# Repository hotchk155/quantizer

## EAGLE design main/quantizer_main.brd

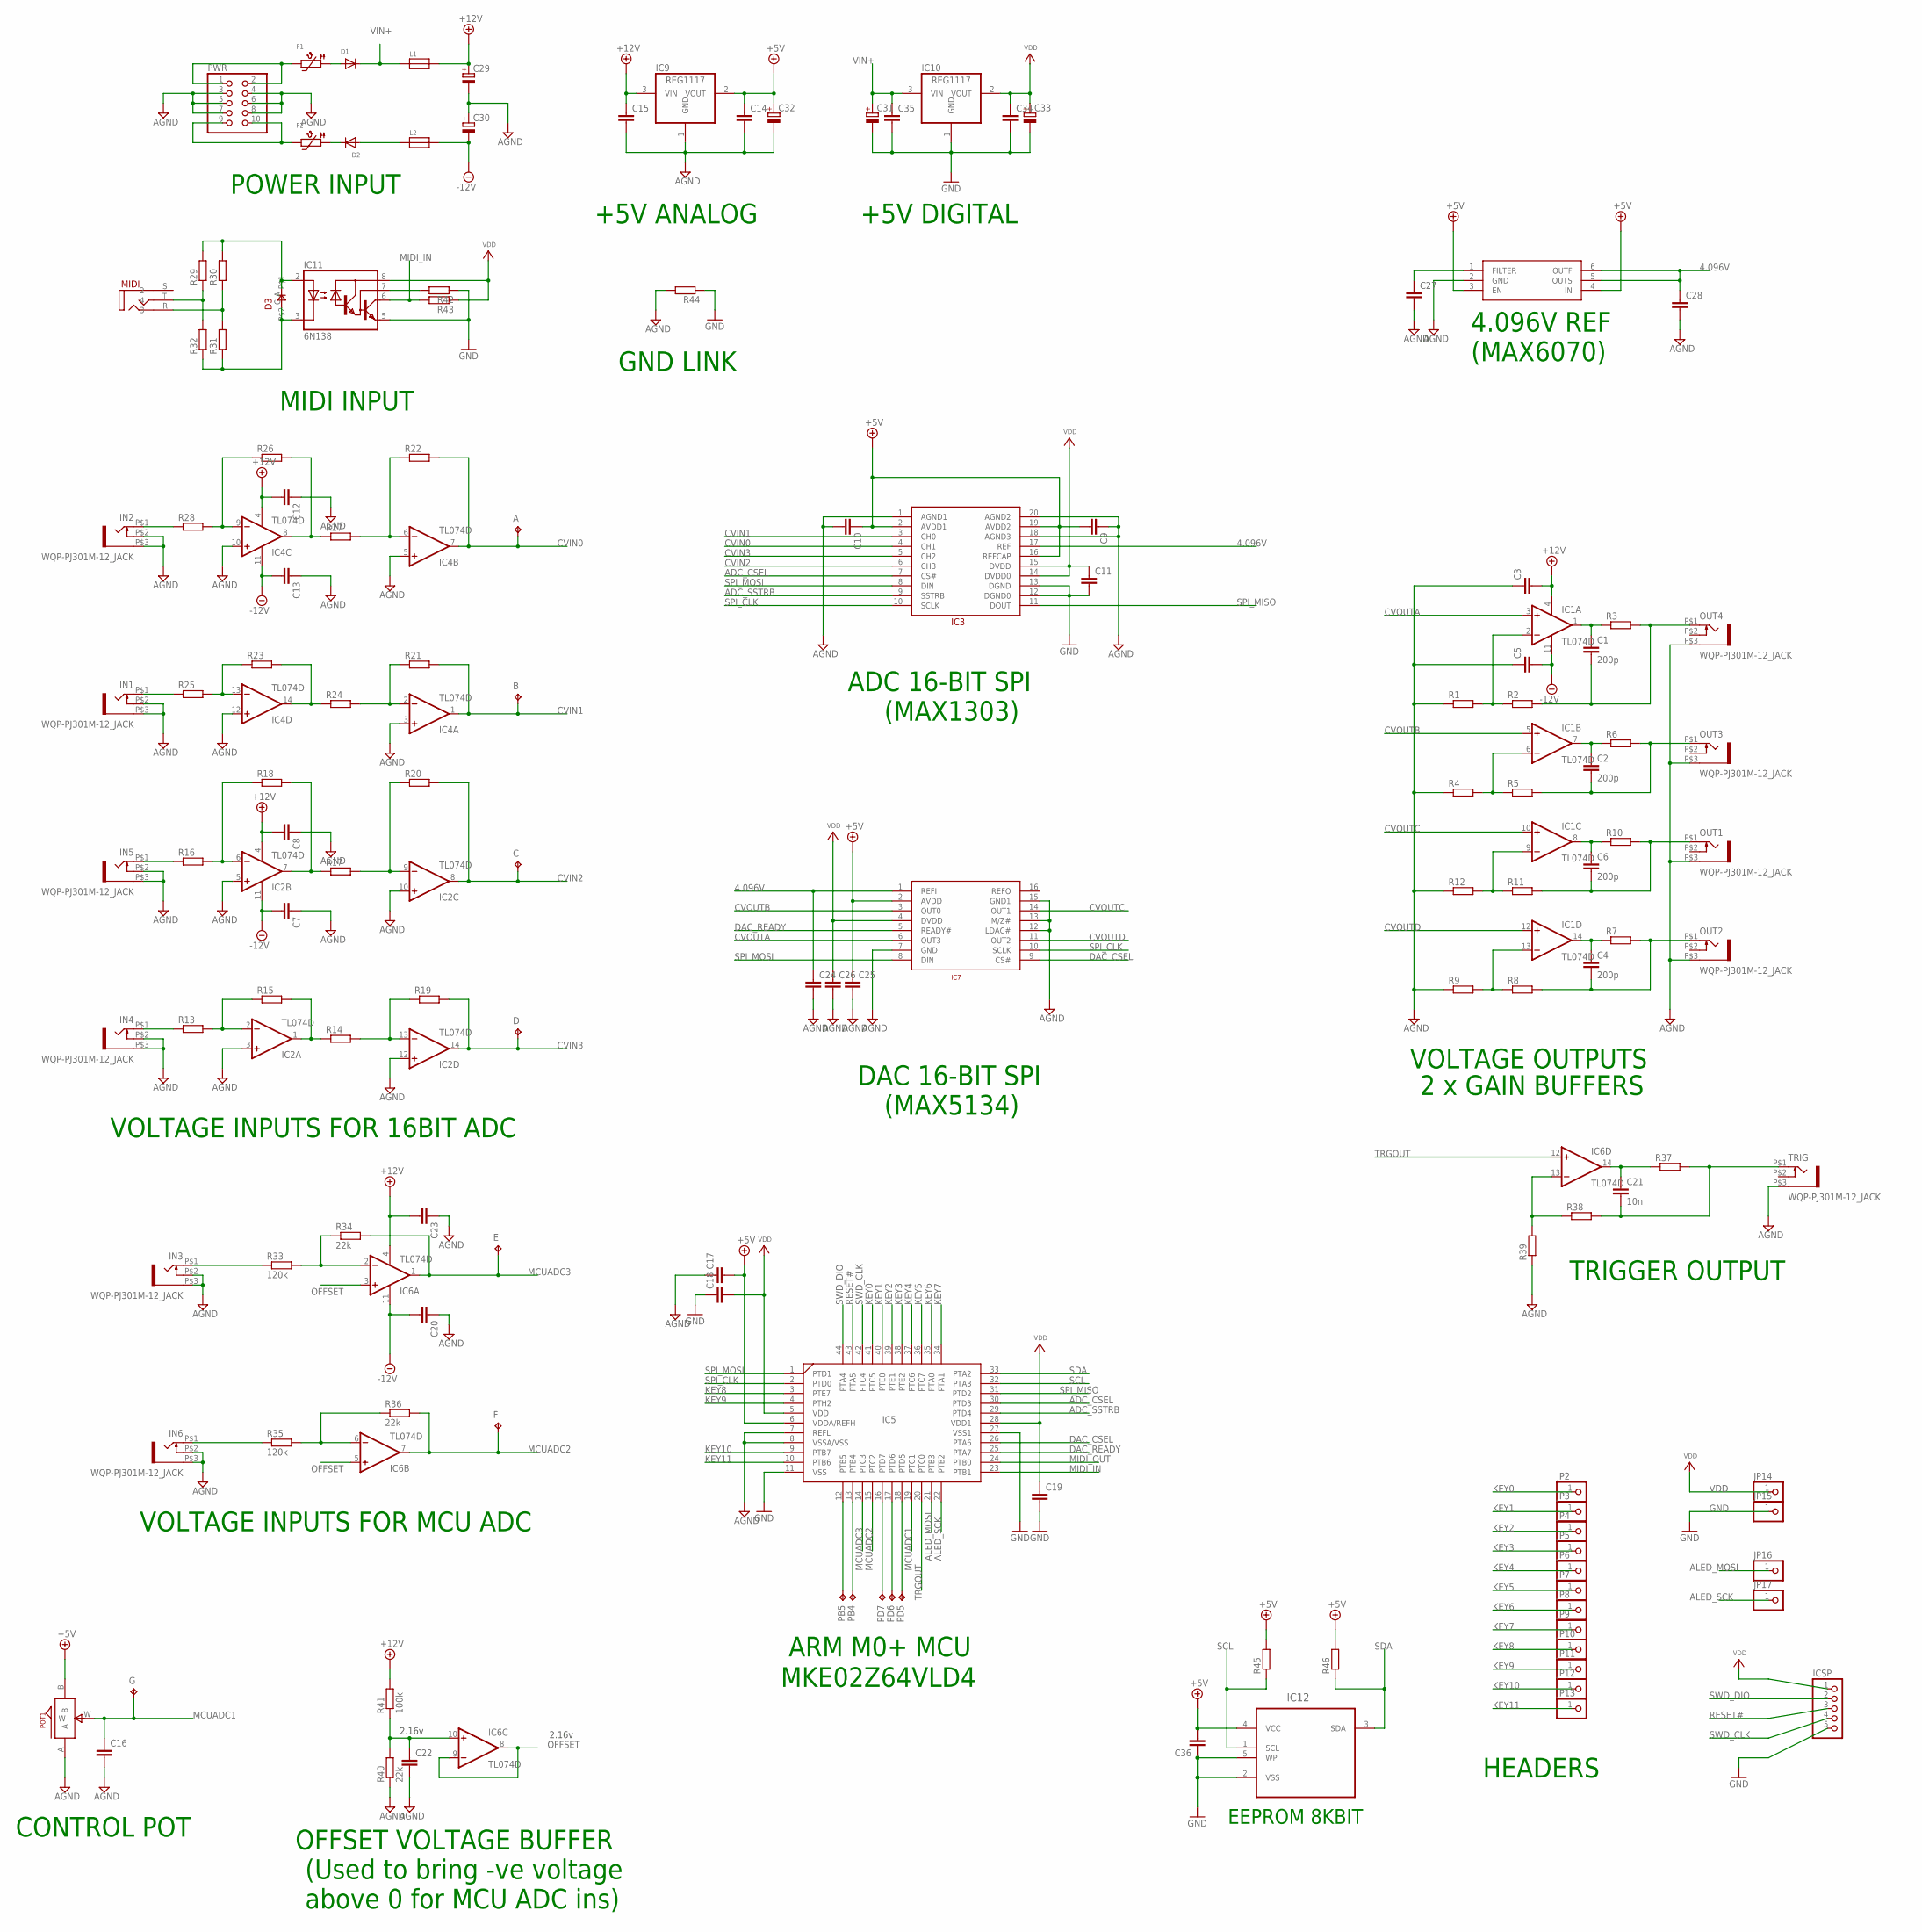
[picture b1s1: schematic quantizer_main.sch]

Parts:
A: TPB1,27; B1,27
B: TPB1,27; B1,27
C: TPB1,27; B1,27
C1, C2, C4, C6: 200p; C0805
C3, C5, C7, C8, C9, C10, C11, C12, C13, C14, C15, C16, C17, C18, C19, C20, C22, C23, C24, C25, C26, C27, C28, C34, C35, C36: C-EUC0805; C0805
C21: 10n; C0805
C29, C30, C31, C32, C33: CPOL-EUE2-5; E2-5
D: TPB1,27; B1,27
D1, D2: DIODESOD-123; SOD-123
D3: 0805DIODE
E: TPB1,27; B1,27
F: TPB1,27; B1,27
F1, F2: PTC1206; 1206
G: TPB1,27; B1,27
IC1, IC2, IC4, IC6: TL074D; SO14
IC3: MAX1303_ADC; TSSOP20
IC5: MKE02_44PIN; TQFP44
IC7: MAX5134_DAC; TSSOP16
IC8: MAX6070; SOT23-6
IC9, IC10: REG1117; SOT223
IC11: 6N138; DIL08
IC12: 24LC_16BT-I/OT; SOT95P290X145-5N
ICSP: PINHD-1X5; 1X05
IN1, IN2, IN3, IN4, IN5, IN6: WQP-PJ301M-12_JACK
JP2, JP3, JP4, JP5, JP6, JP7, JP8, JP9, JP10, JP11, JP12, JP13, JP14, JP15, JP16, JP17: PINHD-1X1; 1X01
L1, L2: FERRITE; 0603
MIDI: VERTICAL_3_5MM_SOCKETTHONK; PJ301CM
OUT1, OUT2, OUT3, OUT4: WQP-PJ301M-12_JACK
PB4, PB5: TPB1,27; B1,27
PD5, PD6, PD7: TPB1,27; B1,27
POT1: ALPS_POT_SMALL; SMALL_ALPS_POT
PWR: PINHD-2X5; 2X05
R1, R2, R3, R4, R5, R6, R7, R8, R9, R10, R11, R12, R13, R14, R15, R16, R17, R18, R19, R20, R21, R22, R23, R24, R25, R26, R27, R28, R29, R30, R31, R32, R37, R38, R39, R42, R43, R44, R45, R46: R-EU_R0805; R0805
R33, R35: 120k; R0805
R34, R36, R40: 22k; R0805
R41: 100k; R0805
TRIG: WQP-PJ301M-12_JACK

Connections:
4.096V: C24.1, C28.1, IC3.17 (REF), IC7.1 (REFI), IC8.5 (OUTS), IC8.6 (OUTF)
+5V: C9.2, C10.1, C14.1, C17.2, C25.1, C32.+, C36.2, IC3.2 (AVDD1), IC3.16 (REFCAP), IC3.19 (AVDD2), IC5.6 (VDDA/REFH), IC7.2 (AVDD), IC8.3 (EN), IC8.4 (IN), IC9.2 (VOUT), IC12.4 (VCC), POT1.B, R45.2, R46.2
+12V: C3.2, C8.2, C12.2, C15.1, C23.2, C29.+, IC1.4 (V+), IC2.4 (V+), IC4.4 (V+), IC6.4 (V+), IC9.3 (VIN), L1.2, R41.2
-12V: C5.2, C7.2, C13.2, C20.2, C30.-, IC1.11 (V-), IC2.11 (V-), IC4.11 (V-), IC6.11 (V-), L2.2
ADC_CSEL: IC3.7 (CS#), IC5.30 (PTD3)
ADC_SSTRB: IC3.9 (SSTRB), IC5.29 (PTD4)
AGND: C3.1, C5.1, C7.1, C8.1, C9.1, C10.2, C12.1, C13.1, C14.2, C15.2, C16.2, C17.1, C20.1, C22.2, C23.1, C24.2, C25.2, C26.2, C27.2, C28.2, C29.-, C30.+, C32.-, IC2.3 (+IN), IC2.5 (+IN), IC2.10 (+IN), IC2.12 (+IN), IC3.1 (AGND1), IC3.18 (AGND3), IC3.20 (AGND2), IC4.3 (+IN), IC4.5 (+IN), IC4.10 (+IN), IC4.12 (+IN), IC5.7 (REFL), IC5.8 (VSSA/VSS), IC7.7 (GND), IC7.12 (LDAC#), IC7.13 (M/Z#), IC7.15 (GND1), IC8.2 (GND), IC9.1 (GND), IN1.P$2 (3), IN1.P$3 (1), IN2.P$2 (3), IN2.P$3 (1), IN3.P$2 (3), IN3.P$3 (1), IN4.P$2 (3), IN4.P$3 (1), IN5.P$2 (3), IN5.P$3 (1), IN6.P$2 (3), IN6.P$3 (1), OUT1.P$3 (1), OUT2.P$3 (1), OUT3.P$3 (1), OUT4.P$3 (1), POT1.A, PWR.3, PWR.4, PWR.5, PWR.6, PWR.7, PWR.8, R1.1, R4.1, R9.1, R12.1, R39.1, R40.1, R44.2, TRIG.P$3 (1)
ALED_MOSI: IC5.21 (PTB3), JP16.1
ALED_SCK: IC5.22 (PTB2), JP17.1
CVIN0: A.TP, IC3.4 (CH1), IC4.7 (OUT), R22.2
CVIN1: B.TP, IC3.3 (CH0), IC4.1 (OUT), R21.2
CVIN2: C.TP, IC2.8 (OUT), IC3.6 (CH3), R20.2
CVIN3: D.TP, IC2.14 (OUT), IC3.5 (CH2), R19.2
CVOUTA: IC1.3 (+IN), IC7.6 (OUT3)
CVOUTB: IC1.5 (+IN), IC7.3 (OUT0)
CVOUTC: IC1.10 (+IN), IC7.14 (OUT1)
CVOUTD: IC1.12 (+IN), IC7.11 (OUT2)
DAC_CSEL: IC5.26 (PTA6), IC7.9 (CS#)
DAC_READY: IC5.25 (PTA7), IC7.5 (READY#)
GND: C11.2, C18.1, C19.2, C31.-, C33.-, C34.2, C35.2, C36.1, IC3.12 (DGND0), IC3.13 (DGND), IC5.11 (VSS), IC5.27 (VSS1), IC10.1 (GND), IC11.5 (GND), IC12.2 (VSS), IC12.5 (WP), ICSP.5, JP15.1, R42.1, R44.1
KEY0: IC5.41 (PTC5), JP2.1
KEY1: IC5.40 (PTE0), JP3.1
KEY2: IC5.39 (PTE1), JP4.1
KEY3: IC5.38 (PTE2), JP5.1
KEY4: IC5.37 (PTC6), JP6.1
KEY5: IC5.36 (PTC7), JP7.1
KEY6: IC5.35 (PTA0), JP8.1
KEY7: IC5.34 (PTA1), JP9.1
KEY8: IC5.3 (PTE7), JP10.1
KEY9: IC5.4 (PTH2), JP11.1
KEY10: IC5.9 (PTB7), JP12.1
KEY11: IC5.10 (PTB6), JP13.1
MCUADC1: C16.1, G.TP, IC5.19 (PTC1), POT1.W
MCUADC2: F.TP, IC5.15 (PTC2), IC6.7 (OUT), R36.2
MCUADC3: E.TP, IC5.14 (PTC3), IC6.1 (OUT), R34.2
MIDI_IN: IC5.23 (PTB1), IC11.6 (VO), R43.2
MIDI_OUT: IC5.24 (PTB0)
unnamed: IC1.2 (-IN), R1.2, R2.1
unnamed: C1.2, OUT4.P$1 (2), R2.2, R3.2
unnamed: D1.A, F1.1
unnamed: C1.1, IC1.1 (OUT), R3.1
unnamed: IN1.P$1 (2), R25.1
unnamed: IC1.6 (-IN), R4.2, R5.1
unnamed: C2.2, OUT3.P$1 (2), R5.2, R6.2
unnamed: C2.1, IC1.7 (OUT), R6.1
unnamed: D2.C, F2.1
unnamed: IN2.P$1 (2), R28.1
unnamed: IC1.9 (-IN), R11.1, R12.2
unnamed: C6.2, OUT1.P$1 (2), R10.2, R11.2
unnamed: C6.1, IC1.8 (OUT), R10.1
unnamed: F1.2, PWR.1, PWR.2
unnamed: IC4.9 (-IN), R26.1, R28.2
unnamed: IC1.13 (-IN), R8.1, R9.2
unnamed: C4.2, OUT2.P$1 (2), R7.2, R8.2
unnamed: C4.1, IC1.14 (OUT), R7.1
unnamed: F2.2, PWR.9, PWR.10
unnamed: IC4.8 (OUT), R26.2, R27.1
unnamed: IC4.6 (-IN), R22.1, R27.2
unnamed: IC5.12 (PTB5), PB5.TP
unnamed: IC11.7 (VB), R42.2
unnamed: MIDI.R (3), R30.1, R31.2
unnamed: IC4.13 (-IN), R23.1, R25.2
unnamed: IC4.14 (OUT), R23.2, R24.1
unnamed: IC4.2 (-IN), R21.1, R24.2
unnamed: MIDI.T (4), R29.1, R32.2
unnamed: D3.C, IC11.3 (C), R31.1, R32.1
unnamed: IN5.P$1 (2), R16.1
unnamed: IC2.6 (-IN), R16.2, R18.1
unnamed: IC2.7 (OUT), R17.1, R18.2
unnamed: IC2.9 (-IN), R17.2, R20.1
unnamed: IC6.13 (-IN), R38.1, R39.2
unnamed: C21.1, IC6.14 (OUT), R37.1
unnamed: IN4.P$1 (2), R13.1
unnamed: IC2.2 (-IN), R13.2, R15.1
unnamed: IC2.1 (OUT), R14.1, R15.2
unnamed: IC2.13 (-IN), R14.2, R19.1
unnamed: C21.2, R37.2, R38.2, TRIG.P$1 (2)
unnamed: D3.A, IC11.2 (A), R29.2, R30.2
unnamed: C22.1, IC6.10 (+IN), R40.2, R41.1
unnamed: IC6.2 (-IN), R33.2, R34.1
unnamed: C27.1, IC8.1 (FILTER)
unnamed: IN3.P$1 (2), R33.1
unnamed: IC6.6 (-IN), R35.2, R36.1
unnamed: IC5.16 (PTD7), PD7.TP
unnamed: IN6.P$1 (2), R35.1
unnamed: IC5.17 (PTD6), PD6.TP
unnamed: IC5.18 (PTD5), PD5.TP
unnamed: IC5.13 (PTB4), PB4.TP
OFFSET: IC6.3 (+IN), IC6.5 (+IN), IC6.8 (OUT), IC6.9 (-IN)
RESET#: IC5.43 (PTA5), ICSP.3
SCL: IC5.32 (PTA3), IC12.1 (SCL), R45.1
SDA: IC5.33 (PTA2), IC12.3 (SDA), R46.1
SPI_CLK: IC3.10 (SCLK), IC5.2 (PTD0), IC7.10 (SCLK)
SPI_MISO: IC3.11 (DOUT), IC5.31 (PTD2)
SPI_MOSI: IC3.8 (DIN), IC5.1 (PTD1), IC7.8 (DIN)
SWD_CLK: IC5.42 (PTC4), ICSP.4
SWD_DIO: IC5.44 (PTA4), ICSP.2
TRGOUT: IC5.20 (PTC0), IC6.12 (+IN)
VDD: C11.1, C18.2, C19.1, C26.1, C33.+, C34.1, IC3.14 (DVDD0), IC3.15 (DVDD), IC5.5 (VDD), IC5.28 (VDD1), IC7.4 (DVDD), IC10.2 (VOUT), IC11.8 (VCC), ICSP.1, JP14.1, R43.1
VIN+: C31.+, C35.1, D1.C, IC10.3 (VIN), L1.1
VIN-: D2.A, L2.1

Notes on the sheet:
MIDI INPUT
POWER INPUT
+5V ANALOG
+5V DIGITAL
GND LINK
4.096V REF
(MAX6070)
ADC 16-BIT SPI
(MAX1303)
DAC 16-BIT SPI
(MAX5134)
ARM M0+ MCU
MKE02Z64VLD4
VOLTAGE OUTPUTS
2 x GAIN BUFFERS
TRIGGER OUTPUT
VOLTAGE INPUTS FOR 16BIT ADC
VOLTAGE INPUTS FOR MCU ADC
OFFSET VOLTAGE BUFFER
(Used to bring -ve voltage above 0 for MCU ADC ins)
CONTROL POT
HEADERS
EEPROM 8KBIT
2.16v

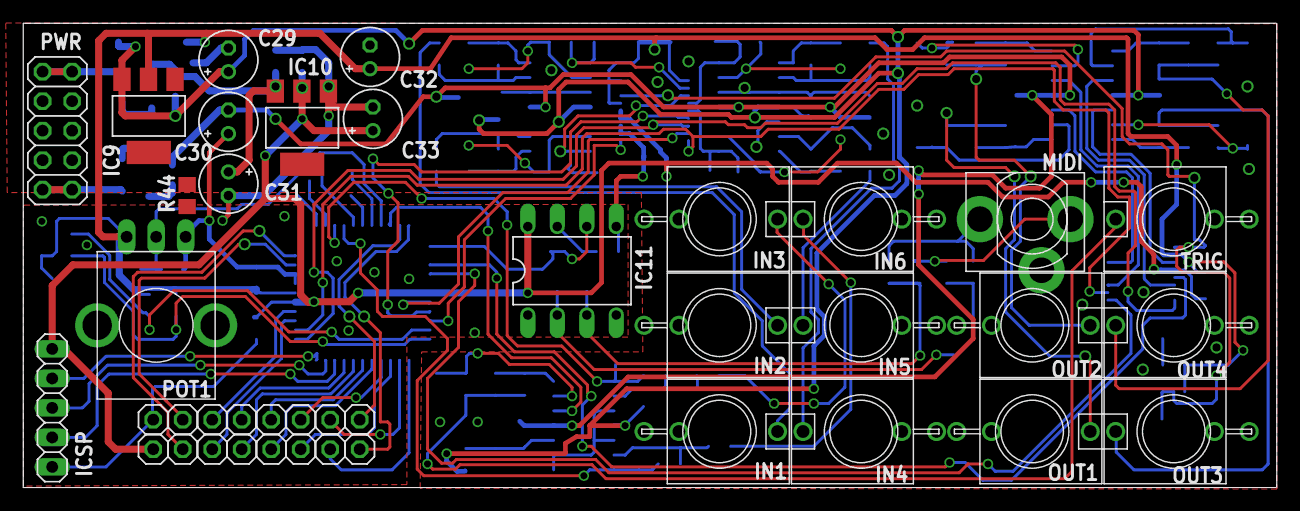
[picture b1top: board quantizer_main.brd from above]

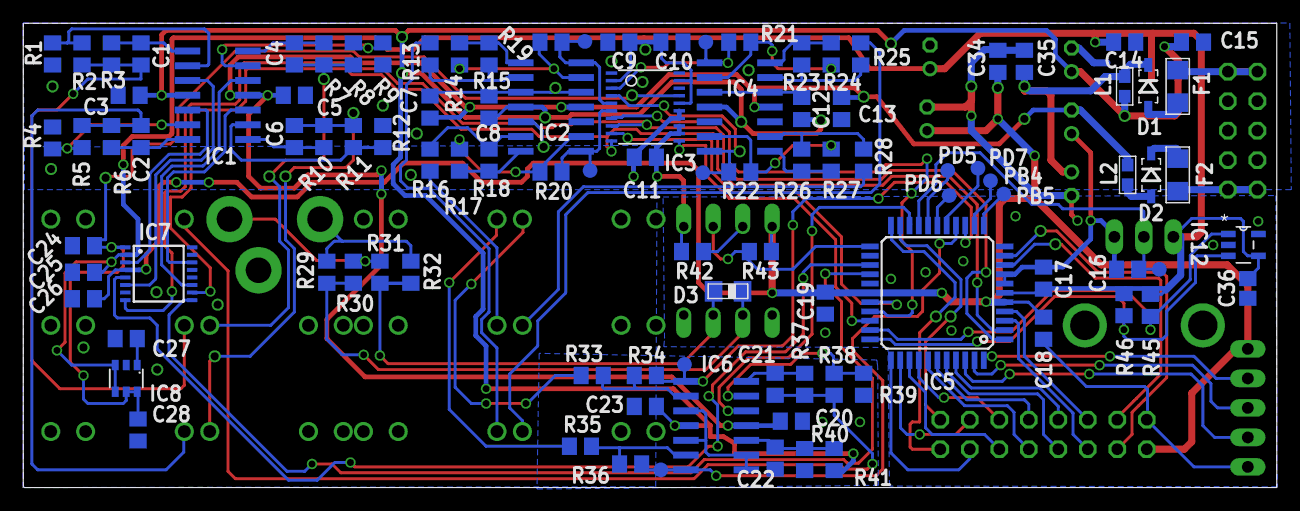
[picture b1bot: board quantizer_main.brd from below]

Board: 2 copper layers, 108.0 x 40.0 mm, 144 parts (104 on the bottom side), 100 nets.

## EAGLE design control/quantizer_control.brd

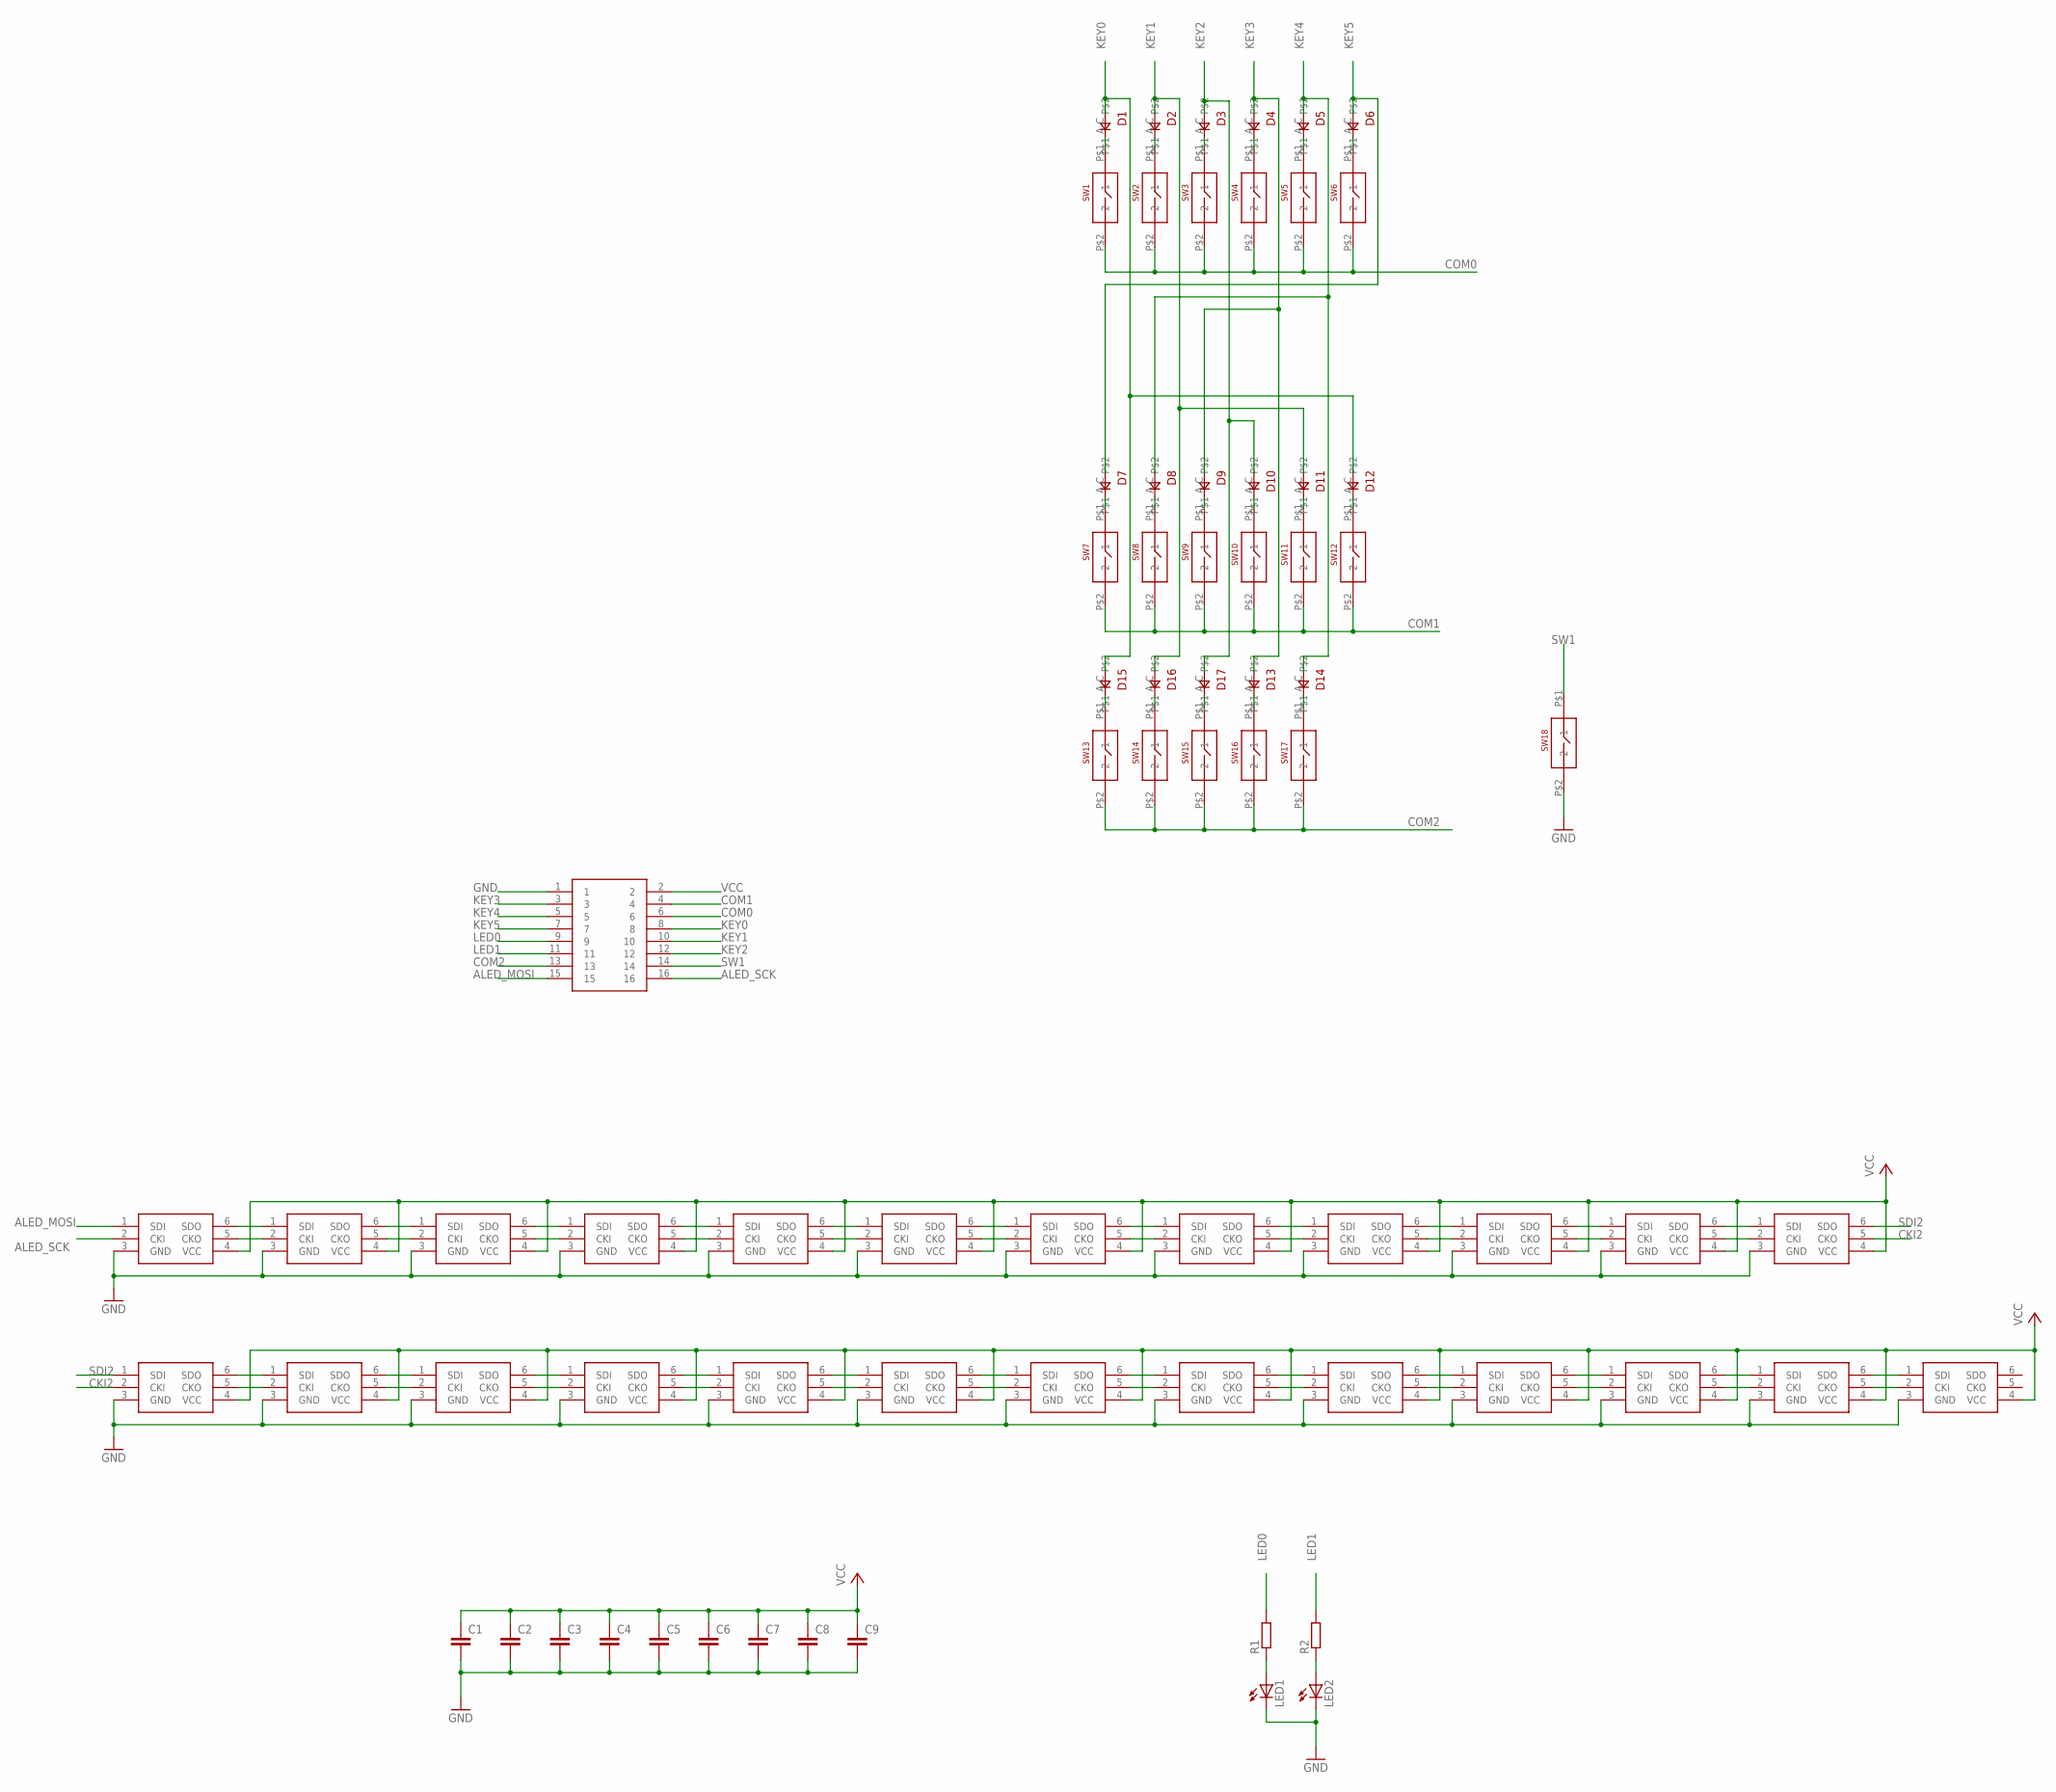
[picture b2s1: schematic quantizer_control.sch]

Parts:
C1, C2, C3, C4, C5, C6, C7, C8, C9: C-EUC0805; C0805
D1, D2, D3, D4, D5, D6, D7, D8, D9, D10, D11, D12, D13, D14, D15, D16, D17: 0805DIODE
LED1, LED2: LEDCHIP-LED0805; CHIP-LED0805
R1, R2: R-EU_R0805; R0805
SW1, SW2, SW3, SW4, SW5, SW6, SW7, SW8, SW9, SW10, SW11, SW12, SW13, SW14, SW15, SW16, SW17, SW18: SKPMSWITCH
U$1: 2X8SMT; 2X8-SMT
U$2, U$3, U$4, U$5, U$6, U$7, U$8, U$9, U$10, U$11, U$13, U$14, U$15, U$16, U$17, U$18, U$19, U$20, U$21, U$22, U$23, U$24, U$25, U$26, U$27: APA102-2020

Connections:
ALED_MOSI: U$1.15, U$2.1 (SDI)
ALED_SCK: U$1.16, U$2.2 (CKI)
CKI2: U$14.5 (CKO), U$15.2 (CKI)
COM0: SW1.P$2 (2), SW2.P$2 (2), SW3.P$2 (2), SW4.P$2 (2), SW5.P$2 (2), SW6.P$2 (2), U$1.6
COM1: SW7.P$2 (2), SW8.P$2 (2), SW9.P$2 (2), SW10.P$2 (2), SW11.P$2 (2), SW12.P$2 (2), U$1.4
COM2: SW13.P$2 (2), SW14.P$2 (2), SW15.P$2 (2), SW16.P$2 (2), SW17.P$2 (2), U$1.13
GND: C1.2, C2.2, C3.2, C4.2, C5.2, C6.2, C7.2, C8.2, C9.2, LED1.C, LED2.C, SW18.P$2 (2), U$1.1, U$2.3 (GND), U$3.3 (GND), U$4.3 (GND), U$5.3 (GND), U$6.3 (GND), U$7.3 (GND), U$8.3 (GND), U$9.3 (GND), U$10.3 (GND), U$11.3 (GND), U$13.3 (GND), U$14.3 (GND), U$15.3 (GND), U$16.3 (GND), U$17.3 (GND), U$18.3 (GND), U$19.3 (GND), U$20.3 (GND), U$21.3 (GND), U$22.3 (GND), U$23.3 (GND), U$24.3 (GND), U$25.3 (GND), U$26.3 (GND), U$27.3 (GND)
KEY0: D1.C, D12.C, D15.C, U$1.8
KEY1: D2.C, D11.C, D16.C, U$1.10
KEY2: D3.C, D10.C, D17.C, U$1.12
KEY3: D4.C, D9.C, D13.C, U$1.3
KEY4: D5.C, D8.C, D14.C, U$1.5
KEY5: D6.C, D7.C, U$1.7
LED0: R1.2, U$1.9
LED1: R2.2, U$1.11
unnamed: U$26.6 (SDO), U$27.1 (SDI)
unnamed: U$26.5 (CKO), U$27.2 (CKI)
unnamed: D1.A, SW1.P$1 (1)
unnamed: D2.A, SW2.P$1 (1)
unnamed: D3.A, SW3.P$1 (1)
unnamed: D4.A, SW4.P$1 (1)
unnamed: D5.A, SW5.P$1 (1)
unnamed: U$2.6 (SDO), U$3.1 (SDI)
unnamed: U$2.5 (CKO), U$3.2 (CKI)
unnamed: D6.A, SW6.P$1 (1)
unnamed: U$3.6 (SDO), U$4.1 (SDI)
unnamed: U$3.5 (CKO), U$4.2 (CKI)
unnamed: U$4.6 (SDO), U$5.1 (SDI)
unnamed: U$4.5 (CKO), U$5.2 (CKI)
unnamed: U$5.6 (SDO), U$6.1 (SDI)
unnamed: U$5.5 (CKO), U$6.2 (CKI)
unnamed: U$6.6 (SDO), U$7.1 (SDI)
unnamed: U$6.5 (CKO), U$7.2 (CKI)
unnamed: U$7.6 (SDO), U$8.1 (SDI)
unnamed: U$7.5 (CKO), U$8.2 (CKI)
unnamed: U$8.6 (SDO), U$9.1 (SDI)
unnamed: U$8.5 (CKO), U$9.2 (CKI)
unnamed: U$9.6 (SDO), U$10.1 (SDI)
unnamed: U$9.5 (CKO), U$10.2 (CKI)
unnamed: U$10.6 (SDO), U$11.1 (SDI)
unnamed: U$10.5 (CKO), U$11.2 (CKI)
unnamed: U$11.6 (SDO), U$13.1 (SDI)
unnamed: U$11.5 (CKO), U$13.2 (CKI)
unnamed: U$13.6 (SDO), U$14.1 (SDI)
unnamed: D7.A, SW7.P$1 (1)
unnamed: U$13.5 (CKO), U$14.2 (CKI)
unnamed: LED1.A, R1.1
unnamed: U$15.6 (SDO), U$16.1 (SDI)
unnamed: U$15.5 (CKO), U$16.2 (CKI)
unnamed: U$16.6 (SDO), U$17.1 (SDI)
unnamed: D8.A, SW8.P$1 (1)
unnamed: U$16.5 (CKO), U$17.2 (CKI)
unnamed: U$17.6 (SDO), U$18.1 (SDI)
unnamed: U$17.5 (CKO), U$18.2 (CKI)
unnamed: U$18.6 (SDO), U$19.1 (SDI)
unnamed: U$18.5 (CKO), U$19.2 (CKI)
unnamed: U$19.6 (SDO), U$20.1 (SDI)
unnamed: U$19.5 (CKO), U$20.2 (CKI)
unnamed: U$20.6 (SDO), U$21.1 (SDI)
unnamed: D9.A, SW9.P$1 (1)
unnamed: U$20.5 (CKO), U$21.2 (CKI)
unnamed: U$21.6 (SDO), U$22.1 (SDI)
unnamed: U$21.5 (CKO), U$22.2 (CKI)
unnamed: D10.A, SW10.P$1 (1)
unnamed: U$22.6 (SDO), U$23.1 (SDI)
unnamed: U$22.5 (CKO), U$23.2 (CKI)
unnamed: U$23.6 (SDO), U$24.1 (SDI)
unnamed: U$23.5 (CKO), U$24.2 (CKI)
unnamed: U$24.6 (SDO), U$25.1 (SDI)
unnamed: U$24.5 (CKO), U$25.2 (CKI)
unnamed: U$25.6 (SDO), U$26.1 (SDI)
unnamed: U$25.5 (CKO), U$26.2 (CKI)
unnamed: LED2.A, R2.1
unnamed: D11.A, SW11.P$1 (1)
unnamed: D12.A, SW12.P$1 (1)
unnamed: D15.A, SW13.P$1 (1)
unnamed: D16.A, SW14.P$1 (1)
unnamed: D17.A, SW15.P$1 (1)
unnamed: D13.A, SW16.P$1 (1)
unnamed: D14.A, SW17.P$1 (1)
SDI2: U$14.6 (SDO), U$15.1 (SDI)
SW1: SW18.P$1 (1), U$1.14
VCC: C1.1, C2.1, C3.1, C4.1, C5.1, C6.1, C7.1, C8.1, C9.1, U$1.2, U$2.4 (VCC), U$3.4 (VCC), U$4.4 (VCC), U$5.4 (VCC), U$6.4 (VCC), U$7.4 (VCC), U$8.4 (VCC), U$9.4 (VCC), U$10.4 (VCC), U$11.4 (VCC), U$13.4 (VCC), U$14.4 (VCC), U$15.4 (VCC), U$16.4 (VCC), U$17.4 (VCC), U$18.4 (VCC), U$19.4 (VCC), U$20.4 (VCC), U$21.4 (VCC), U$22.4 (VCC), U$23.4 (VCC), U$24.4 (VCC), U$25.4 (VCC), U$26.4 (VCC), U$27.4 (VCC)

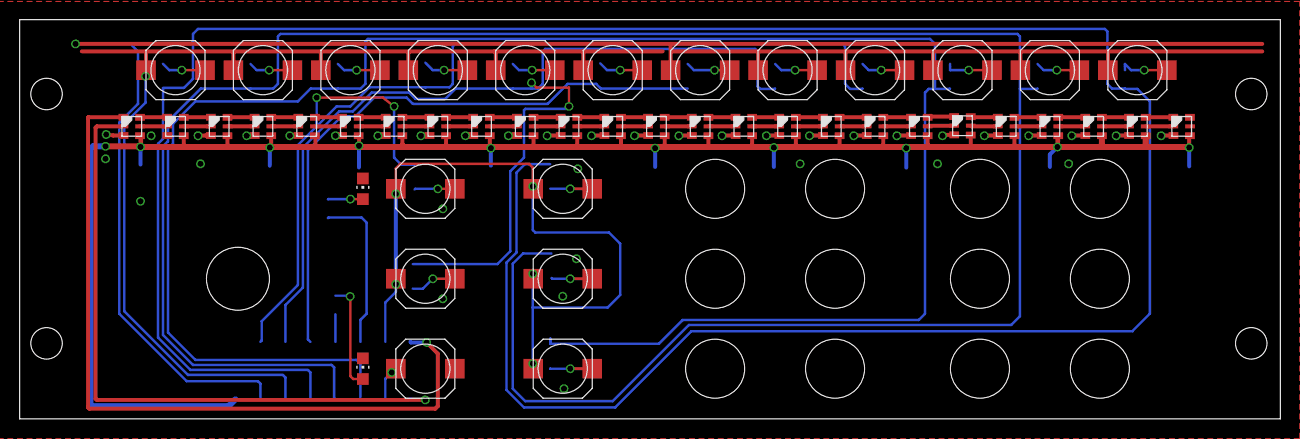
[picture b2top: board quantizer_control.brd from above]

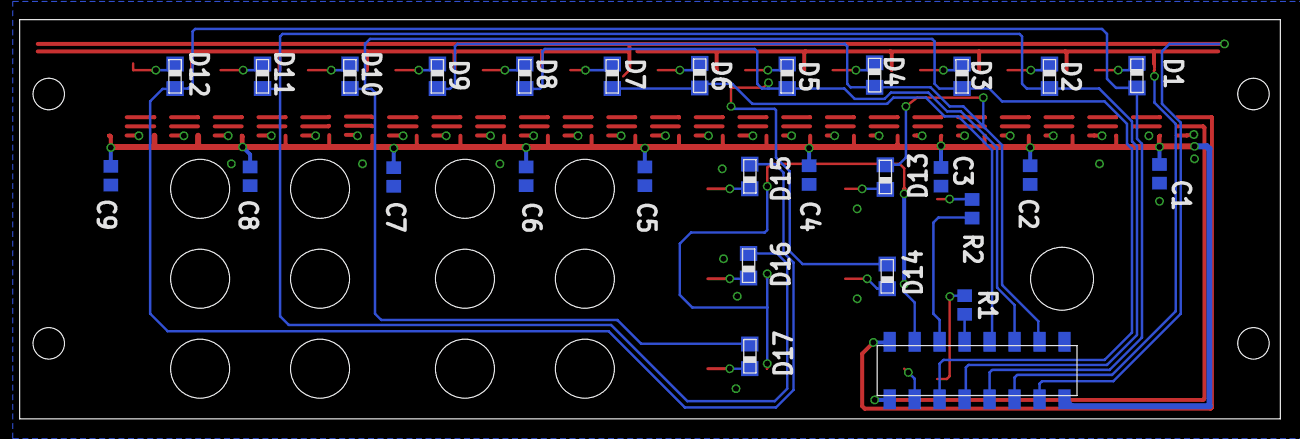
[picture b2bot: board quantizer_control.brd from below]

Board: 2 copper layers, 128.2 x 40.6 mm, 74 parts (29 on the bottom side), 83 nets.

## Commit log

2019-07-08 sddd
2019-07-10 v1 pcb?
2019-07-11 tweaks... v1 for fab
2019-07-11 silkscreen tweaks
2019-08-19 c21 10n
2019-08-19 initial commit of firmware proj
2019-09-09 worky
2019-09-09 spi cs ckludge
2019-09-09 dsfsf
2019-09-09 sdfdfs
2019-09-11 sdfsdf
2019-09-11 dgdfg
2019-09-12 ewewew
2019-09-12 ffdffd
2019-09-15 assd
2019-09-15 asasas
2019-10-28 starting on adc stuff
2019-10-28 adc stuff
